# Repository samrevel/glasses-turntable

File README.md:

# glasses-turntable
This repository has the code, schematic, board. etc for the electronics of the glasses turntable kiosk display in Revel Digital warehouse 13.

The glasses turntable electronics board (board) uses a ATmega8 microcontroller to controll a H bridge that controlls a brushed DC motor. The DC motor has a gear boc to slow the motor down and to increase torqu. The motor turns the whole display. The display is ran from a 12V dc source and is fused. All the logic on the board is running 5V.

On the board there are connector for LEDs (12V LED string), power (2.1X5.5mm barrel jack center positive 12V), homing switch, extranal button (not used), mbrushed DC motor, serial, programmer conncetor, and fan (12V power out, not used). 

The display will rotate when the board recives a serial command. There serial commands are sent by a display located need the glasses turntable. When the board recives a command it will return the same serial command back.

Serial settings:
- Buad: 9600
- Bits: 8
- Stop Bits: 1
- Parity: None
- Flow Control: None
- Data format: ASCII
- Ending charachers: None (will not hurt if send it)

Serial commands (in ASCII):
- "1" rotate to side 1
- "2" rotate to side 2
- "3" rotate to side 3
- "4" rotate for about a second
- "5" rotate for about a second backwares
- "6" rotate for about a haft second
- "7" rotate for about a haft backwares

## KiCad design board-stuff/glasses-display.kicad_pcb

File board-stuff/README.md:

This is all the file that is use to design the electrionics. Everything was make using KiCad and left all the KiCad project file. 
There is also a PDF of the schematic so you can look at it if you dont have KiCad. There are the PCB gerber files too.

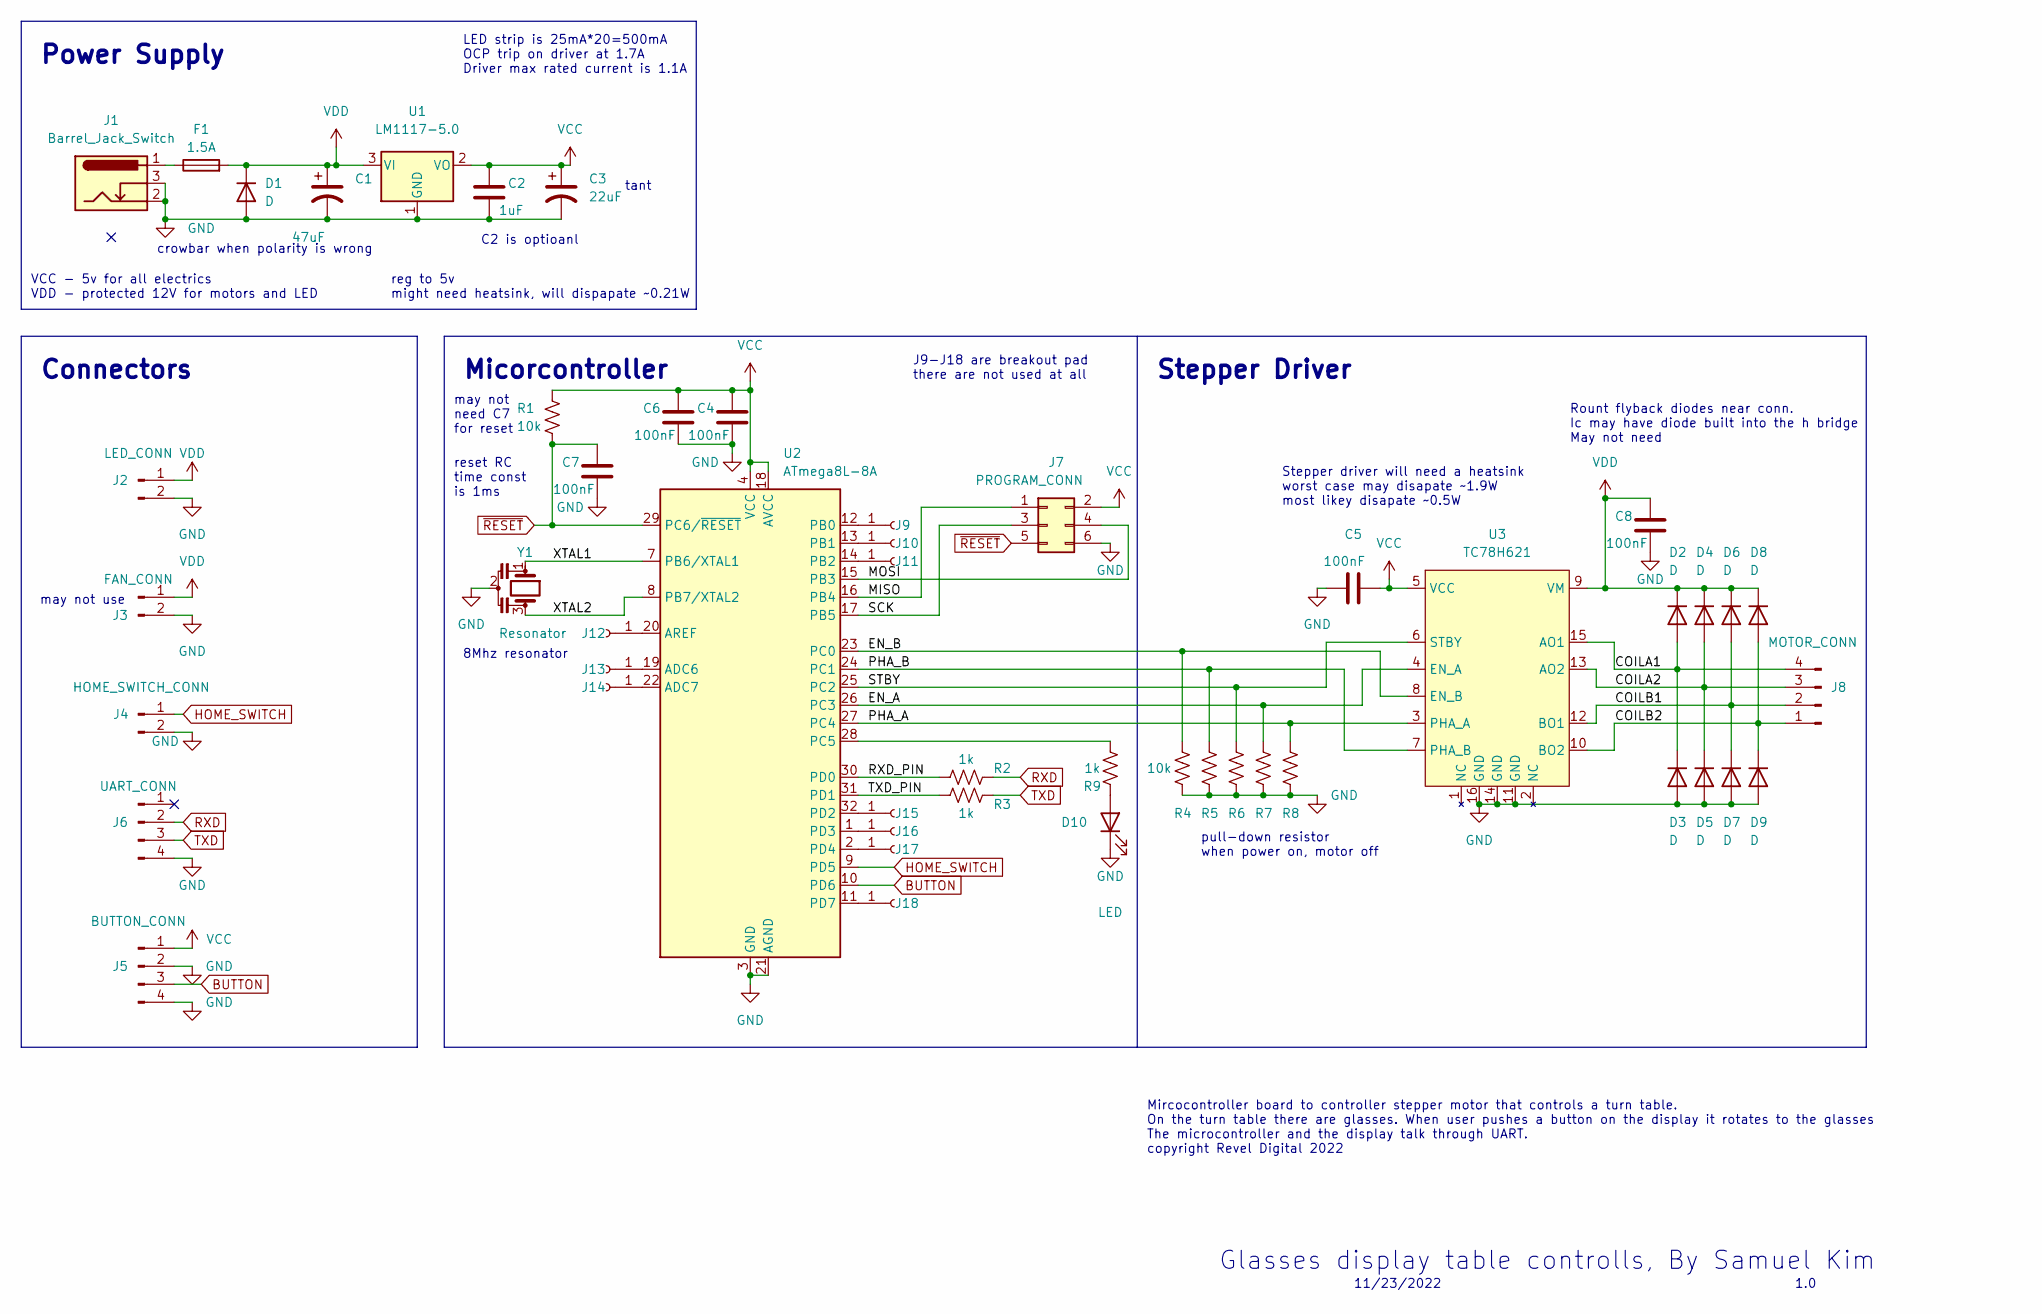
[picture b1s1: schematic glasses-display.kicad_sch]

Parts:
C1: 47uF; CP_Elec_6.3x5.2
C2: 1uF; R_0805_2012Metric
C3: 22uF; CP_EIA-3528-12_Kemet-T
C4, C5, C6, C7, C8: 100nF; R_0603_1608Metric
D1: D; D_SMB
D2, D3, D4, D5, D6, D7, D8, D9: D; D_SOD-323
D10: LED; LED_0603_1608Metric
F1: 1.5A; R_1206_3216Metric
J1: Barrel_Jack_Switch; BarrelJack_GCT_DCJ200-10-A_Horizontal
J2: LED_CONN; JST_EH_B2B-EH-A_1x02_P2.50mm_Vertical
J3: FAN_CONN; JST_EH_B2B-EH-A_1x02_P2.50mm_Vertical
J4: HOME_SWITCH_CONN; JST_EH_B2B-EH-A_1x02_P2.50mm_Vertical
J5: BUTTON_CONN; JST_EH_B4B-EH-A_1x04_P2.50mm_Vertical
J6: UART_CONN; JST_EH_B4B-EH-A_1x04_P2.50mm_Vertical
J7: PROGRAM_CONN; PinSocket_2x03_P2.54mm_Vertical
J8: MOTOR_CONN; JST_EH_B4B-EH-A_1x04_P2.50mm_Vertical
J9, J10, J11, J12, J13, J14, J15, J16, J17, J18: PAD; SolderWirePad_1x01_SMD_1x2mm
R1, R4, R5, R6, R7, R8: 10k; R_0603_1608Metric
R2, R3, R9: 1k; R_0603_1608Metric
U1: LM1117-5.0; SOT-223-3_TabPin2
U2: ATmega8L-8A; TQFP-32_7x7mm_P0.8mm
U3: TC78H621; TSSOP-16_4.4x5mm_P0.65mm
Y1: Resonator; Resonator_SMD_Murata_CSTxExxV-3Pin_3.0x1.1mm_HandSoldering

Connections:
/COILA1: D2.2 (A), D3.1 (K), J8.4, U3.15 (AO1)
/COILA2: D4.2 (A), D5.1 (K), J8.3, U3.13 (AO2)
/COILB1: D6.2 (A), D7.1 (K), J8.2, U3.12 (BO1)
/COILB2: D8.2 (A), D9.1 (K), J8.1, U3.10 (BO2)
/EN_A: R7.1, U2.26 (PC3), U3.4 (EN_A)
/EN_B: R4.1, U2.23 (PC0), U3.8 (EN_B)
/MISO: J7.1, U2.16 (PB4)
/MOSI: J7.4, U2.15 (PB3)
/PHA_A: R8.1, U2.27 (PC4), U3.3 (PHA_A)
/PHA_B: R5.1, U2.24 (PC1), U3.7 (PHA_B)
/RXD_PIN: R2.1, U2.30 (PD0)
/SCK: J7.3, U2.17 (PB5)
/STBY: R6.1, U2.25 (PC2), U3.6 (STBY)
/TXD_PIN: R3.1, U2.31 (PD1)
/XTAL1: U2.7 (PB6/XTAL1), Y1.1
/XTAL2: U2.8 (PB7/XTAL2), Y1.3
BUTTON: J5.3, U2.10 (PD6)
GND: C1.2, C2.2, C3.2, C4.2, C5.1, C6.2, C7.2, C8.2, D1.2 (A), D3.2 (A), D5.2 (A), D7.2 (A), D9.2 (A), D10.1 (K), J1.2, J1.3, J2.2, J3.2, J4.2, J5.2, J5.4, J6.4, J7.6, R4.2, R5.2, R6.2, R7.2, R8.2, U1.1 (GND), U2.3 (GND), U2.5 (GND), U2.21 (AGND), U3.11 (GND), U3.14 (GND), U3.16 (GND), Y1.2
HOME_SWITCH: J4.1, U2.9 (PD5)
unnamed: D10.2 (A), R9.2
unnamed: F1.1, J1.1
unnamed: J9.1, U2.12 (PB0)
unnamed: J10.1, U2.13 (PB1)
unnamed: J11.1, U2.14 (PB2)
unnamed: J12.1, U2.20 (AREF)
unnamed: J13.1, U2.19 (ADC6)
unnamed: J14.1, U2.22 (ADC7)
unnamed: J15.1, U2.32 (PD2)
unnamed: J16.1, U2.1 (PD3)
unnamed: J17.1, U2.2 (PD4)
unnamed: J18.1, U2.11 (PD7)
unnamed: R9.1, U2.28 (PC5)
RXD: J6.2, R2.2
TXD: J6.3, R3.2
VCC: C2.1, C3.1, C4.1, C5.2, C6.1, J5.1, J7.2, R1.1, U1.2 (VO), U2.4 (VCC), U2.6 (VCC), U2.18 (AVCC), U3.5 (VCC)
VDD: C1.1, C8.1, D1.1 (K), D2.1 (K), D4.1 (K), D6.1 (K), D8.1 (K), F1.2, J2.1, J3.1, U1.3 (VI), U3.9 (VM)
~RESET: C7.1, J7.5, R1.2, U2.29 (PC6/~RESET)

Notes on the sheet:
may not need C7 for reset
C2 is optioanl
crowbar when polarity is wrong
Stepper driver will need a heatsink worst case may disapate ~1.9W most likey disapate ~0.5W
reset RC time const is 1ms
reg to 5v might need heatsink, will dispapate ~0.21W
LED strip is 25mA*20=500mA OCP trip on driver at 1.7A Driver max rated current is 1.1A
8Mhz resonator
pull-down resistor when power on, motor off
J9-J18 are breakout pad there are not used at all
11/23/2022
Mircocontroller board to controller stepper motor that controls a turn table. On the turn table there are glasses. When user pushes a button on the display it rotates to the glasses The microcontroller and the display talk through UART. copyright Revel Digital 2022
1.0
Glasses display table controlls, By Samuel Kim
Micorcontroller
may not use
tant
Connectors
Stepper Driver
VCC - 5v for all electrics VDD - protected 12V for motors and LED
Rount flyback diodes near conn. Ic may have diode built into the h bridge May not need
Power Supply

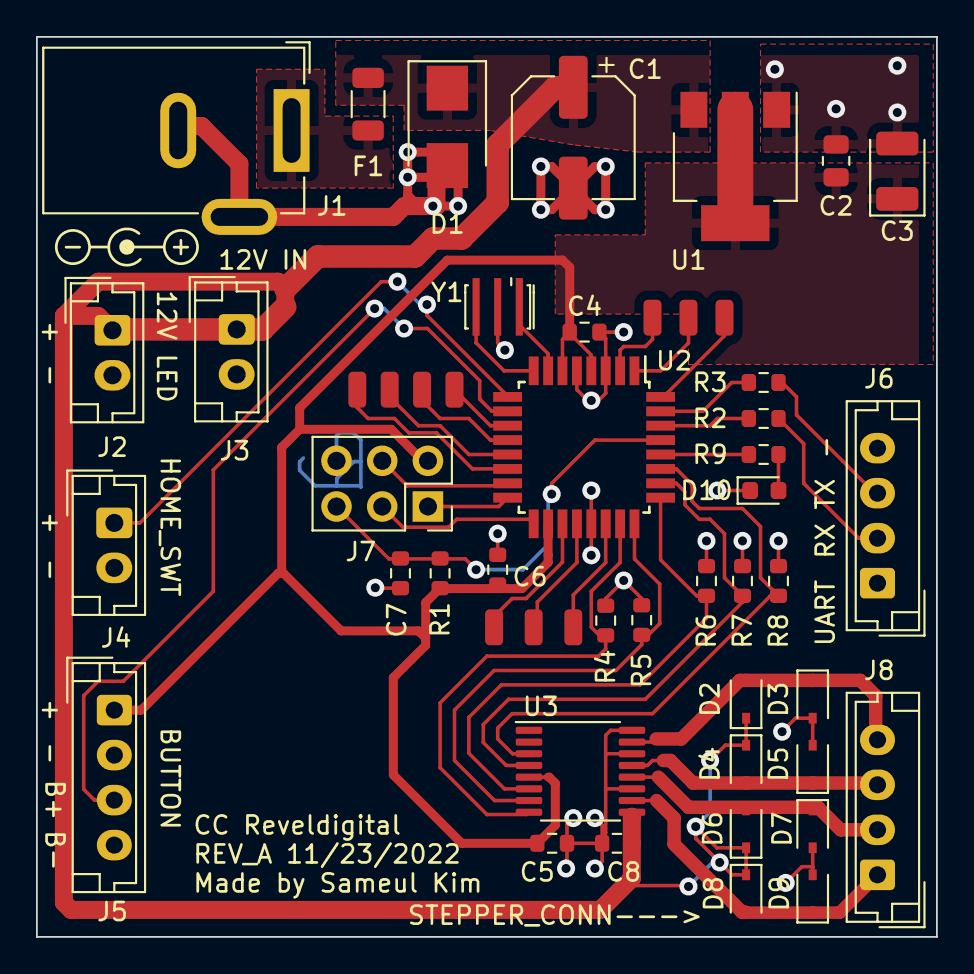
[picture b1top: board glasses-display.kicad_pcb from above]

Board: 2 copper layers, 50.0 x 50.0 mm, 50 parts (0 on the bottom side), 37 nets.

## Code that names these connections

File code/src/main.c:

// using the atmega8l microcontroller
// Datasheet: http://ww1.microchip.com/downloads/en/DeviceDoc/atmel-2486-8-bit-avr-microcontroller-atmega8_l_datasheet.pdf
// dual brushed dc motor/stepper driver chip is TC78H621FNG
// Datasheet: https://toshiba.semicon-storage.com/info/TC78H621FNG_datasheet_en_20170410.pdf?did=57992&prodName=TC78H621FNG

#include <avr/io.h>
#include <util/delay.h>
#include <stdbool.h> // i want to use bool
#define byte uint8_t // i like using byte, i can remeber what it is

// ------------ PINS --------------------------
// all pins for the motor H-brigde driver is connected to port C
// this is using
// PC0 - EN_B, PC3 - EN_A
// PC1 - PHA_B, PC4 - PHA_A
// PC2 - STBY, PC5 - LED
// motor B is not used
#define MPORT PORTC
#define MPORTD DDRC
#define EN_B 0b00000001
#define EN_A 0b00001000
#define PHA_B 0b00000010
#define PHA_A 0b00010000
#define STBY 0b00000100
#define LED 0b00100000

// Inputs
// PD6 - BUTTON (need pullup res)
// PD5 - HOME_SWITCH (need pullup res)
// PD0 - RXD, PD1 - TXD
#define BUTTON 0b01000000
#define HOME_SWITCH 0b00100000

// motor speed
// degs is calc with the motor speed of 40rpm
#define DELAY_START 100
#define DELAY_360D 1500
#define DELAY_180D 750
#define DELAY_120D 500
#define DELAY_EX1 125 // adjust the delay to account for the insersha of the turntable and gearbox ans stop speed
#define DELAY_EX2 150 // adjust the delay to account for the insersha
#define DELAY_EX3 100 // adjust the delay to account for the insersha
#define DELAY_240D 1000
#define DELAY_STOP 0 // not driving motor backware to stop it

// Set up serial
#define FOSC F_CPU // Clock Speed, 8MHz extranal
#define BAUD 9600
#define MYUBRR FOSC / 16 / BAUD - 1

// DDRx   - Used to configure the respective PORT as output/input
// PORTx  - Used to write the data to the Port pins
// PINx   - Used to Read the data from the port pins

// init serial func, right from the datasheet page 135
void USART_Init(unsigned int ubrr)
{
  /* Set baud rate */
  UBRRH = (unsigned char)(ubrr >> 8);
  UBRRL = (unsigned char)ubrr;
  /* Enable receiver and transmitter */
  UCSRB = (1 << RXEN) | (1 << TXEN);
  /* Set frame format: 8data, 1stop bit */
  UCSRC = (1 << URSEL) | /* (1 << USBS) |*/ (3 << UCSZ0);
}

// serial receive func, right from the datasheet page 139
unsigned char USART_Receive(void) // may change to return byte instead of char, makes things ez later
{
  /* Wait for data to be received */
  while (!(UCSRA & (1 << RXC)))
    ;
  /* Get and return received data from buffer */
  return UDR;
}

// serial printing, just for testing
void USART_Transmit(unsigned char data)
{
  /* Wait for empty transmit buffer */
  while (!(UCSRA & (1 << UDRE)))
    ;
  /* Put data into buffer, sends the data */
  UDR = data;
}

// this function rotoates the motor
// int delay - runs the motor for the number of ms, negitive numbers rotate backware
// bool home - when true the motor stops when it gets a home trigger, false will ignor the home trigger
// bool slow - when true the motor runs at 50% duly at 500 hz, false the motor runs normal.
void rotate(int delay, bool home, bool slow)
{
  // turn off motor
  if (delay == 0)
  {
    PORTC = 0;
    return;
  }

  if (delay > 0)
  {
    PORTC = (EN_A | STBY | LED);
    for (int i = 0; i < delay; i++)
    {
      _delay_ms(1); // delay to let motor run
      if (slow)
      {
        PORTC = PORTC ^ EN_A;
      }

      if (home)
      {
        if (!(PIND & (HOME_SWITCH))) // check to see if it is homes
        {
          PORTC = 0; // turn off motor
          return;    // when the HOME_SWITCH goes low (when it is pressed). it will break out of for loop
        }
      }
    }
  }
  else
  {
    PORTC = (EN_A | STBY | LED | PHA_A);
    for (int i = 0; i > delay; i--)
    {
      _delay_ms(1); // delay to let motor run
      if (slow)
      {
        PORTC = PORTC ^ EN_A;
      }
      if (home)
      {
        if (!(PIND & (HOME_SWITCH))) // check to see if it is homes
        {
          PORTC = 0;
          return; // when the HOME_SWITCH goes low (when it is pressed). it will break out of for loop
        }
      }
    }
  }
  PORTC = 0; // turn off the motor
  return;
}

int main()
{
  //  set motor pins as outputs
  DDRC = 0b00111111;
  // turn off all motor pins
  PORTC = 0b00000000;

  // enable inputs as inputs
  DDRD = 0b00000000;
  // enable pullup resistors
  PORTD = (BUTTON | HOME_SWITCH);

  // init serial
  USART_Init(MYUBRR);
  // rotate(-1,1,1);

  while (1)
  {

    switch (USART_Receive())
    {
    case '\n': // ingor termiator chars
    case '\r':
      break;
    case '1': // rotate to side 1
      USART_Transmit('1');
      if (!(PIND & (HOME_SWITCH))) // when home switch is low, that means it is homed
      {
        rotate(DELAY_180D, false, false); // rotate out of the way of the
      }
      rotate(DELAY_START + DELAY_360D, true, false); // find where home is
      rotate(DELAY_180D, false, false);              // move more to home a 2nd time
      rotate(DELAY_360D, true, false);               // find where home is
      rotate(DELAY_EX1, false, false);               // rotate to the right side
      // rotate(DELAY_STOP, false, false); // stop motor
      PORTC = 0; // turn off motor
      break;
    case '2': // rotate to side 2
      USART_Transmit('2');
      if (!(PIND & (HOME_SWITCH))) // when home switch is low, that means it is homed
      {
        rotate(DELAY_180D, false, false); // go backwares to get more persice position of the home
      }
      rotate(DELAY_START + DELAY_360D, true, false); // find where home is
      rotate(DELAY_180D, false, false);              // move more to home a 2nd time
      rotate(DELAY_360D, true, false);               // find where home is
      rotate(DELAY_120D + DELAY_EX2, false, false);  // move to the right side of the display
      // rotate(DELAY_STOP, false, false); // stop motor
      PORTC = 0; // turn off motor
      break;
    case '3': // rotate to side 3
      USART_Transmit('3');
      if (!(PIND & (HOME_SWITCH))) // when home switch is low, that means it is homed
      {
        rotate(DELAY_180D, false, false); // go backwares to get more persice position of the home
      }
      rotate(DELAY_START + DELAY_360D, true, false); // find where home is
      rotate(DELAY_180D, false, false);              // move more to home a 2nd time
      rotate(DELAY_360D, true, false);               // find where home is
      rotate(DELAY_240D + DELAY_EX3, false, false);  // move to the right side of the display
      // rotate(DELAY_STOP, false, false); // stop motor
      PORTC = 0; // turn off motor
      break;
    case '4': // rotate forward for 500ms
      USART_Transmit('4');
      rotate(500, false, false);
      PORTC = 0; // turn off motor
      break;
    case '5': // rotate backwares for 500ms
      USART_Transmit('5');
      rotate(-500, false, false);
      PORTC = 0; // turn off motor
      break;
    case '6': // rotate forward for 250ms
      USART_Transmit('6');
      rotate(250, false, false);
      PORTC = 0; // turn off motor
      break;
    case '7': // rotate backwares for 250ms
      USART_Transmit('7');
      rotate(-250, false, false);
      PORTC = 0; // turn off motor
      break;
    case '8':
      USART_Transmit('8');
      PORTC = 0; // turn off motor
      break;
    default:
      break;
    }
  }
}

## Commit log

2022-11-29 upload the electronics board stuff
2023-01-09 Delete text.txt
    forgot to delete a long time ago, nothing important.
